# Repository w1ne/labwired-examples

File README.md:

# LabWired Examples

Real firmware, inspectable circuit diagrams, reproducible simulator oracles, and (when relevant) parametric mechanical models in [KernelCAD](https://kernelcad.com/).

This repository is for runnable hardware verification stories, **not concept art or untested AI-generated designs**. Each example states which behavior was verified, where the simulator approximates hardware, and what remains missing.

## Catalog

| Example | Firmware and electronics | Mechanics | Evidence |
| --- | --- | --- | --- |
| [ESP32-C3 OLED device — Rev A candidate](examples/displays/esp32c3-oled/) | XIAO ESP32C3 clock demo, native KiCad 10 routed carrier, full BOM and pinned firmware | Removable enclosure source and STEP/STL/3MF; full path/review checks remain unresolved | 5/5 ROM-boot assertions, matching browser-WASM frames, zero native ERC/DRC findings; no physical prototype |
| [Game Boy-compatible handheld](examples/gaming/gameboy-handheld/) | STM32F411 C firmware runs Peanut-GB and an original ROM; ILI9341 and eight controls | Shared carrier/case interfaces, attached exact-source KiCad board, 59 CAD parts and 58 fixed mates | Saved-project MCU verification, host ROM behavior, browser input, hosted native PCB DRC/attachment and static CAD checks; no physical hardware |
| [HeyPCB imported-board acceptance sample](examples/pcb/heypcb-import-acceptance/) | Seven pinned KiCad PCB files and model-gap evidence; no full-board pass | No mechanical model | Source blobs verified; seven imports reported in unmerged PR #2934; none completely simulated |
| [Industrial BLDC fault verification](examples/industrial/bldc-fault-verification/) | STM32L476 compiled C, 24 V motor plant, three digital fault flags, inverter shutdown | No mechanical model in this example | Normal spin-up and 3 fault scenarios model-verified; ideal MCU supply, no physical bench |
| [Quadrotor co-design](examples/robotics/quadrotor-bldc/) | Four STM32L476 C channels; separate native six-layer ESC with zero configured ERC/DRC findings | 36-part KernelCAD frame and four rotor joints; populated-board assembly candidate remains blocked | Candidate browser: 360 exact motor/CAD observations, isolated fault, pause and reset. Actual board simulation and flight remain open. |
| [Pathfinder hobby rocket](examples/aerospace/pathfinder-rocket/) | STM32F411 saved firmware/diagram/stimuli; 5/5 saved flight-sequence oracle clauses | Linked CAD; PCB is wider than the stated available sled width | Saved model-verified firmware; **PCB fit and physical flight blocked** |
| [AXIOM H1 humanoid controller](examples/robotics/axiom-h1/) | ESP32-C3 + two PCA9685 expanders; 20 powered servo command models and fault/E-stop evidence | 20 source-derived CAD bindings; 59 sampled poses and archived mesh replay pass | Saved powered topology; mechanical deployment pending; **physical acceptance failed** |
| [A1 mini printer](examples/fabrication/a1-mini-printer/) | STM32F411 four-axis firmware, endstops, heaters and display; 2/2 saved clauses | Linked printer CAD; native cross-domain acceptance pending | Saved firmware verified; **machine/assembly behavior unverified** |
| [P.I.G. robot arm](examples/robotics/pig-arm/) | Six PCA9685 servo channels, nine poses, limits and E-stop; 3/3 saved clauses | Physical motion/kinematics not accepted | Saved controller verified; **joint actuation not verified** |

## Featured video

[Watch the 75-second quadrotor co-design engineering preview](examples/robotics/quadrotor-bldc/media/quadrotor-engineering-preview.mp4): editable CAD, exploded assembly, native schematic/PCB, four live motor channels, a selected-channel fault, pause and reset. This is actual application footage of a candidate STM32 propulsion bench. The physical OpenESC board and aircraft flight are not simulated by that bench.

## Run

Open an example directory. The export-backed packs contain the saved LabWired firmware, circuit, stimuli, and requirements in `project.input.json`, plus revision-pinned evidence in `evidence.json`. They link to existing saved projects. Some require separate linked PCB/CAD assets or further integration. An import does **not** imply the original evidence transfers to the new project. The quadrotor and other engineering demos additionally include native sources and recorded tools.

For an introduction to firmware-aware circuit simulation, use the [LabWired circuit simulator guide](https://labwired.com/circuit-simulator/). It links to a GPIO-to-RC oscilloscope demonstration and explains the different browser linear-circuit and native ngspice capabilities. The quadrotor example above is a separate motor-control verification. For imported circuits, see the [KiCad PCB simulation guide](https://labwired.com/kicad-pcb-simulation/) and the [ESP32-S3 BME280 source-net case](https://labwired.com/kicad-pcb-simulation/#bme280-i2c-address). Import is not whole-board simulation.

## Contribution standard

New examples need catalog-validated connectivity, compilable firmware, an explicit test oracle, and precise model limits. For mechanical projects, keep editable KernelCAD source and verified joints. See [CONTRIBUTING.md](CONTRIBUTING.md).

**Core simulator and firmware-model changes belong in [w1ne/labwired-core](https://github.com/w1ne/labwired-core).** This repository stores reproducible consumers of that engine, not copies of the engine.

## Licensing

Example source and scripts are MIT licensed. Individual CAD assets may carry CC0-1.0 declarations in their metadata. Manufacturer names (including ODrive) are descriptive and do not imply endorsement, compatibility or use of proprietary software.

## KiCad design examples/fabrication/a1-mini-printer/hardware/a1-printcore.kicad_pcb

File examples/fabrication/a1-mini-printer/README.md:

# A1 mini four-axis printer

This example is exported from a **real saved LabWired project**, not a proposed design.

- [Open the original project in LabWired](https://app.labwired.com/p/4926352279d2673187b55cd5e727ff69/edit)
- [Project source, diagram, stimuli and oracle input](project.input.json)
- [Revision-pinned saved evidence](evidence.json)
- Board: `stm32f411ceu6-blackpill`
- Saved content hash: `63c92bacf144cf5ed240425d4828d8a97b2cbc9203688dc901eb56fc9221a980`
- Original simulator evidence on this exact revision: **model_verified**
- Individual saved requirement results: **2/2 verified**

## Reproduce

1. Inspect `project.input.json`, which contains the original editable firmware source, circuit/netlist, input stimuli and explicit verification requirements.
2. Use LabWired's `labwired_project_create` with the input fields, or open the original saved project above. The imported copy is **unlisted**, and it does not automatically inherit a PCB, CAD attachment or verification receipt.
3. Run `labwired_project_verify` against the copied project with the saved requirements. Inspect the returned exact content hash and all clause results. Do not treat compilation alone as verified.
4. Inspect PCB and mechanical artifacts separately in the original project; record a fresh verification when changing firmware, wiring, source, or CAD identity.

## Proven boundary

Homing, step-command counts, OLED rendering and an overtemperature fail-safe are verified in the firmware twin; live machine mechanics, PCB-to-assembly equivalence, true extrusion and physical printer operation are not.

The linked PCB/CAD items, if present, are **not** reconstructed by the project-input import. The `evidence.json` file is a readback of the original saved project on 2026-11-21, not a promise that any future deployment or new copy has passed.

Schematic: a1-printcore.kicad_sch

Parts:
C1, C2: 12p; C_0603_1608Metric
C3: 2.2u; C_0805_2012Metric
C4, C5, C6, C7, C9, C10, C30, C31, C33, C40, C41, C43, C50, C51, C53, C60, C61, C63, C106, C120: 100n; C_0603_1608Metric
C8, C107: 1u; C_0805_2012Metric
C32, C42, C52, C62: 220n; C_0603_1608Metric
C34, C44, C54, C64: 100n/50V; C_0805_2012Metric
C35, C45, C55, C65: 47u/50V; C_1210_3225Metric
C100: 470u/35V; CP_Elec_10x10.5
C101: 1u/50V; C_1210_3225Metric
C102, C103: 4.7u/50V; C_1210_3225Metric
C104, C105: 22u/10V; C_1210_3225Metric
C109, C110: 4.7u; C_0805_2012Metric
C112: 220n/50V; C_0603_1608Metric
C140, C141, C142, C143, C144: 10n; C_0603_1608Metric
D1: SMBJ33A; D_SMB
D3, D4: SS34; D_SMA
D10: PWR; LED_0603_1608Metric
D11: FAULT; LED_0603_1608Metric
F1: 25A MINI; Fuseholder_Blade_Mini_Keystone_3568
J1: 24V INPUT; AMASS_XT30PW-M_1x02_P2.50mm_Horizontal
J2: BED 24V/12A; TerminalBlock_Phoenix_MKDS-3-2-5.08_1x02_P5.08mm_Horizontal
J3: HOTEND 24V/3A; TerminalBlock_Phoenix_MKDS-3-2-5.08_1x02_P5.08mm_Horizontal
J4: FAN1; JST_XH_B2B-XH-A_1x02_P2.50mm_Vertical
J5: FAN2; JST_XH_B2B-XH-A_1x02_P2.50mm_Vertical
J10: X_MOTOR; Molex_Micro-Fit_3.0_43650-0410_1x04-1MP_P3.00mm_Horizontal
J11: Y_MOTOR; Molex_Micro-Fit_3.0_43650-0410_1x04-1MP_P3.00mm_Horizontal
J12: Z_MOTOR; Molex_Micro-Fit_3.0_43650-0410_1x04-1MP_P3.00mm_Horizontal
J13: E_MOTOR; Molex_Micro-Fit_3.0_43650-0410_1x04-1MP_P3.00mm_Horizontal
J20: USB4216-03-A; MPN USB4216-03-A
J21: SWD; PinHeader_2x05_P1.27mm_Vertical_SMD
J22: OLED I2C; JST_SH_BM04B-SRSS-TB_1x04-1MP_P1.00mm_Vertical
J23: UART; JST_SH_BM04B-SRSS-TB_1x04-1MP_P1.00mm_Vertical
J30: X END; JST_XH_B3B-XH-A_1x03_P2.50mm_Vertical
J31: Y END; JST_XH_B3B-XH-A_1x03_P2.50mm_Vertical
J32: Z END; JST_XH_B3B-XH-A_1x03_P2.50mm_Vertical
J33: BED NTC; JST_XH_B2B-XH-A_1x02_P2.50mm_Vertical
J34: HOT NTC; JST_XH_B2B-XH-A_1x02_P2.50mm_Vertical
J35: ESTOP/START; JST_XH_B4B-XH-A_1x04_P2.50mm_Vertical
L1: 10uH/3.2A; L_Bourns_SRN6045TA
Q1, Q2, Q3: AOD4184A; TO-252-3_TabPin2
Q4, Q5: AO3400A; SOT-23
R1, R33, R43, R53, R63, R105, R140, R141, R142, R152, R153: 10k; R_0603_1608Metric
R2, R100, R103, R121, R123, R125, R128, R129: 100k; R_0603_1608Metric
R3, R4: 22R; R_0603_1608Metric
R5, R6: 5.1k; R_0603_1608Metric
R7: 1M; R_0603_1608Metric
R30, R31, R40, R41, R50, R51, R60, R61: 0.10R; R_2512_6332Metric
R32, R42, R52, R62: 30.1k; R_0603_1608Metric
R34, R44, R54, R64, R104: 24.9k; R_0603_1608Metric
R120, R122, R124: 33R; R_0603_1608Metric
R126, R127: 100R; R_0603_1608Metric
R143, R144: 100k 0.1%; R_0603_1608Metric
R150, R151: 4.7k; R_0603_1608Metric
R160, R161: 1k; R_0603_1608Metric
SW1: RESET; SW_SPST_PTS810
TP1: X_VREF; TestPoint_Pad_D1.5mm
TP2: Y_VREF; TestPoint_Pad_D1.5mm
TP3: Z_VREF; TestPoint_Pad_D1.5mm
TP4: E_VREF; TestPoint_Pad_D1.5mm
TP20: 24V; TestPoint_Pad_D1.5mm
TP21: 5V; TestPoint_Pad_D1.5mm
TP22: 3V3; TestPoint_Pad_D1.5mm
TP23: GND; TestPoint_Pad_D1.5mm
U1: STM32F411CEU6; QFN-48-1EP_7x7mm_P0.5mm_EP5.6x5.6mm
U10, U11, U12, U13: A4988SETTR-T; TQFN-28-1EP_5x5mm_P0.5mm_EP3.25x3.25mm
U20: LMR36520A; SOIC-8-1EP_3.9x4.9mm_P1.27mm_EP2.41x3.3mm
U21: AP2112K-3.3; SOT-23-5
U30: 74HCT125D; SOIC-14_3.9x8.7mm_P1.27mm
U31: USBLC6-2SC6; SOT-23-6
Y1: 8MHz; Crystal_SMD_3225-4Pin_3.2x2.5mm

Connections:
+3V3: C4.1, C5.1, C6.1, C7.1, C8.1, C9.1, C10.1, C33.1, C43.1, C53.1, C63.1, C110.1, J21.1, J22.2 (VCC), J23.2, J30.2, J31.2, J32.2, J33.1 (A), J34.1 (A), J35.4, R1.1, R32.1, R42.1, R52.1, R62.1, R105.1, R140.1, R141.1, R142.1, R150.1, R151.1, R152.1, R153.1, R160.1, R161.1, TP22.1, U1.1 (VBAT), U1.9 (VDDA), U1.24 (VDD), U1.36 (VDD), U1.48 (VDD), U10.12 (RESET), U10.14 (SLEEP), U10.15 (VDD), U11.12 (RESET), U11.14 (SLEEP), U11.15 (VDD), U12.12 (RESET), U12.14 (SLEEP), U12.15 (VDD), U13.12 (RESET), U13.14 (SLEEP), U13.15 (VDD), U21.5 (VOUT)
+5V: C104.1, C105.1, C109.1, C120.1, L1.2, R103.1, TP21.1, U21.1 (VIN), U21.3 (EN), U30.14 (VCC)
+24V: C31.2, C34.1, C35.1, C41.2, C44.1, C45.1, C51.2, C54.1, C55.1, C61.2, C64.1, C65.1, C100.1, C101.1, C102.1, C103.1, C112.1, D1.1 (K), D3.1 (K), D4.1 (K), F1.2, J2.1, J3.1, J4.1 (+), J5.1, R100.1, TP20.1, U10.22 (VMOT), U10.28 (VMOT), U11.22 (VMOT), U11.28 (VMOT), U12.22 (VMOT), U12.28 (VMOT), U13.22 (VMOT), U13.28 (VMOT), U20.2 (VIN)
+24VIN: F1.1, J1.1 (+)
BED_CMD: U1.27 (PB14), U30.5
BED_GATE: R120.1, R122.1, U30.6
BED_GATE_A: Q1.1 (G), R120.2, R121.1
BED_GATE_B: Q2.1 (G), R122.2, R123.1
BED_SW: J2.2, Q1.2 (D), Q2.2 (D)
BOOT0: R2.1, U1.44 (BOOT0)
BUCK_BOOT: C106.1, U20.7 (BOOT)
BUCK_EN: R100.2, U20.3 (EN)
BUCK_FB: R103.2, R104.1, U20.5 (FB)
BUCK_PG: R105.2, U20.4 (PG)
BUCK_SW: C106.2, L1.1, U20.8 (SW)
BUCK_VCC: C107.1, U20.6 (VCC)
CC1: J20.A5 (3), R5.1
CC2: J20.B5 (4), R6.1
DRV_EN: U1.25 (PB12), U10.2 (EN), U11.2 (EN), U12.2 (EN), U13.2 (EN)
END_X: C140.1, J30.3, R140.2, U1.29 (PA8)
END_Y: C141.1, J31.3, R141.2, U1.2 (PC13)
END_Z: C142.1, J32.3, R142.2, U1.3 (PC14)
ESTOP: J35.2, R152.2, U1.20 (PB2)
E_A+: J13.1 (1A), U13.24 (1A)
E_A-: J13.2 (1B), U13.21 (1B)
E_B+: J13.3 (2A), U13.26 (2A)
E_B-: J13.4 (2B), U13.1 (2B)
E_CP1: C60.1, U13.4 (CP1)
E_CP2: C60.2, U13.5 (CP2)
E_DIR: U1.21 (PB10), U13.19 (DIR)
E_ROSC: R64.1, U13.13 (ROSC)
E_S1: R60.1, U13.23 (SENSE1)
E_S2: R61.1, U13.27 (SENSE2)
E_STEP: U1.46 (PB9), U13.16 (STEP)
E_VCP: C61.1, U13.6 (VCP)
E_VREF: R62.2, R63.1, TP4.1, U13.17 (REF)
E_VREG: C62.1, U13.8 (VREG)
FAN1_CMD: U1.28 (PB15), U30.9
FAN1_GATE: R126.1, U30.8
FAN1_GATE_Q: Q4.1 (G), R126.2, R128.1
FAN1_SW: D3.2 (A), J4.2 (-), Q4.3 (D)
FAN2_CMD: U1.10 (PA0), U30.12
FAN2_GATE: R127.1, U30.11
FAN2_GATE_Q: Q5.1 (G), R127.2, R129.1
FAN2_SW: D4.2 (A), J5.2, Q5.3 (D)
GND: C1.2, C2.2, C3.2, C4.2, C5.2, C6.2, C7.2, C8.2, C9.2, C10.2, C32.2, C33.2, C34.2, C35.2, C42.2, C43.2, C44.2, C45.2, C52.2, C53.2, C54.2, C55.2, C62.2, C63.2, C64.2, C65.2, C100.2, C101.2, C102.2, C103.2, C104.2, C105.2, C107.2, C109.2, C110.2, C112.2, C120.2, C140.2, C141.2, C142.2, C143.2, C144.2, D1.2 (A), D10.1 (K), J1.2 (-), J20.A1 (1), J20.A12 (1), J20.B1 (1), J20.B12 (1), J20.SH (1), J21.3, J21.5 (3), J21.9 (3), J22.1 (GND), J23.1, J30.1, J31.1, J32.1, J35.1, Q1.3 (S), Q2.3 (S), Q3.3 (S), Q4.2 (S), Q5.2 (S), R2.2, R5.2, R6.2, R7.2, R30.2, R31.2, R33.2, R34.2, R40.2, R41.2, R43.2, R44.2, R50.2, R51.2, R53.2, R54.2, R60.2, R61.2, R63.2, R64.2, R104.2, R121.2, R123.2, R125.2, R128.2, R129.2, R143.2, R144.2, SW1.2, TP23.1, U1.8 (VSSA), U1.23 (VSS), U1.35 (VSS), U1.47 (VSS), U1.49 (VSS), U10.3 (GND), U10.9 (MS1), U10.10 (MS2), U10.11 (MS3), U10.18 (GND), U10.29 (GND), U11.3 (GND), U11.9 (MS1), U11.10 (MS2), U11.11 (MS3), U11.18 (GND), U11.29 (GND), U12.3 (GND), U12.9 (MS1), U12.10 (MS2), U12.11 (MS3), U12.18 (GND), U12.29 (GND), U13.3 (GND), U13.9 (MS1), U13.10 (MS2), U13.11 (MS3), U13.18 (GND), U13.29 (GND), U20.1 (PGND), U20.9 (PAD), U21.2 (GND), U30.1, U30.4, U30.7 (GND), U30.10, U30.13, U31.2 (GND), Y1.2, Y1.4
HOTEND_CMD: U1.26 (PB13), U30.2
HOT_GATE: R124.1, U30.3
HOT_GATE_Q: Q3.1 (G), R124.2, R125.1
HOT_SW: J3.2, Q3.2 (D)
I2C_SCL: J22.3 (SCL), R150.2, U1.42 (PB6)
I2C_SDA: J22.4 (SDA), R151.2, U1.43 (PB7)
LED_FAULT_A: D11.2 (A), R161.2
LED_PWR_A: D10.2 (A), R160.2
NC_LDO: U21.4 (NC)
NC_PC15: U1.4 (PC15)
NC_SBU1: J20.A8 (7)
NC_SBU2: J20.B8 (8)
NC_SWD7: J21.7 (6)
NC_SWD8: J21.8 (7)
NRST: J21.10 (8), R1.2, SW1.1, U1.7 (NRST)
OSC_IN: C1.1, U1.5 (PH0), Y1.1
OSC_OUT: C2.1, U1.6 (PH1), Y1.3
SPI_MISO: U1.16 (PA6)
SPI_MOSI: U1.17 (PA7)
SPI_SCK: U1.15 (PA5)
START: J35.3, R153.2, U1.38 (PA15)
SWCLK: J21.4, U1.37 (PA14)
SWDIO: J21.2, U1.34 (PA13)
TH_BED: C143.1, J33.2 (B), R143.1, U1.11 (PA1)
TH_HOT: C144.1, J34.2 (B), R144.1, U1.14 (PA4)
UART_RX: J23.4, U1.13 (PA3)
UART_TX: J23.3, U1.12 (PA2)
USB_DM: R3.2, U1.32 (PA11)
USB_DM_CONN: J20.A7 (6), J20.B7 (6), U31.1 (IO1_A)
USB_DM_MCU: R3.1, U31.6 (IO1_B)
USB_DP: R4.2, U1.33 (PA12)
USB_DP_CONN: J20.A6 (5), J20.B6 (5), U31.3 (IO2_A)
USB_DP_MCU: R4.1, U31.4 (IO2_B)
USB_VBUS: J20.A4 (2), J20.A9 (2), J20.B4 (2), J20.B9 (2), U31.5 (VBUS)
USB_VBUS_SENSE: R7.1, U1.30 (PA9)
USER_AUX: D11.1 (K), U1.31 (PA10)
VCAP1: C3.1, U1.22 (VCAP_1)
X_A+: J10.1 (1A), U10.24 (1A)
X_A-: J10.2 (1B), U10.21 (1B)
X_B+: J10.3 (2A), U10.26 (2A)
X_B-: J10.4 (2B), U10.1 (2B)
X_CP1: C30.1, U10.4 (CP1)
X_CP2: C30.2, U10.5 (CP2)
X_DIR: U1.19 (PB1), U10.19 (DIR)
X_ROSC: R34.1, U10.13 (ROSC)
X_S1: R30.1, U10.23 (SENSE1)
X_S2: R31.1, U10.27 (SENSE2)
X_STEP: U1.18 (PB0), U10.16 (STEP)
X_VCP: C31.1, U10.6 (VCP)
X_VREF: R32.2, R33.1, TP1.1, U10.17 (REF)
X_VREG: C32.1, U10.8 (VREG)
Y_A+: J11.1 (1A), U11.24 (1A)
Y_A-: J11.2 (1B), U11.21 (1B)
Y_B+: J11.3 (2A), U11.26 (2A)
Y_B-: J11.4 (2B), U11.1 (2B)
Y_CP1: C40.1, U11.4 (CP1)
Y_CP2: C40.2, U11.5 (CP2)
Y_DIR: U1.40 (PB4), U11.19 (DIR)
Y_ROSC: R44.1, U11.13 (ROSC)
Y_S1: R40.1, U11.23 (SENSE1)
Y_S2: R41.1, U11.27 (SENSE2)
Y_STEP: J21.6 (5), U1.39 (PB3), U11.16 (STEP)
Y_VCP: C41.1, U11.6 (VCP)
Y_VREF: R42.2, R43.1, TP2.1, U11.17 (REF)
Y_VREG: C42.1, U11.8 (VREG)
Z_A+: J12.1 (1A), U12.24 (1A)
Z_A-: J12.2 (1B), U12.21 (1B)
Z_B+: J12.3 (2A), U12.26 (2A)
Z_B-: J12.4 (2B), U12.1 (2B)
Z_CP1: C50.1, U12.4 (CP1)
Z_CP2: C50.2, U12.5 (CP2)
Z_DIR: U1.45 (PB8), U12.19 (DIR)
Z_ROSC: R54.1, U12.13 (ROSC)
Z_S1: R50.1, U12.23 (SENSE1)
Z_S2: R51.1, U12.27 (SENSE2)
Z_STEP: U1.41 (PB5), U12.16 (STEP)
Z_VCP: C51.1, U12.6 (VCP)
Z_VREF: R52.2, R53.1, TP3.1, U12.17 (REF)
Z_VREG: C52.1, U12.8 (VREG)

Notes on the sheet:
MCU / USB
POWER INPUT / REGULATORS
X AXIS
Y AXIS
Z AXIS
EXTRUDER
HEATERS / FANS
I/O / CONTROLS
J10 MP x2: mechanical retention, no net
J11 MP x2: mechanical retention, no net
J12 MP x2: mechanical retention, no net
J13 MP x2: mechanical retention, no net
J22 MP x2: mechanical retention, no net
J23 MP x2: mechanical retention, no net
External supply intent: J1 24 V through F1; USB host VBUS; common return. Flags are nonphysical.

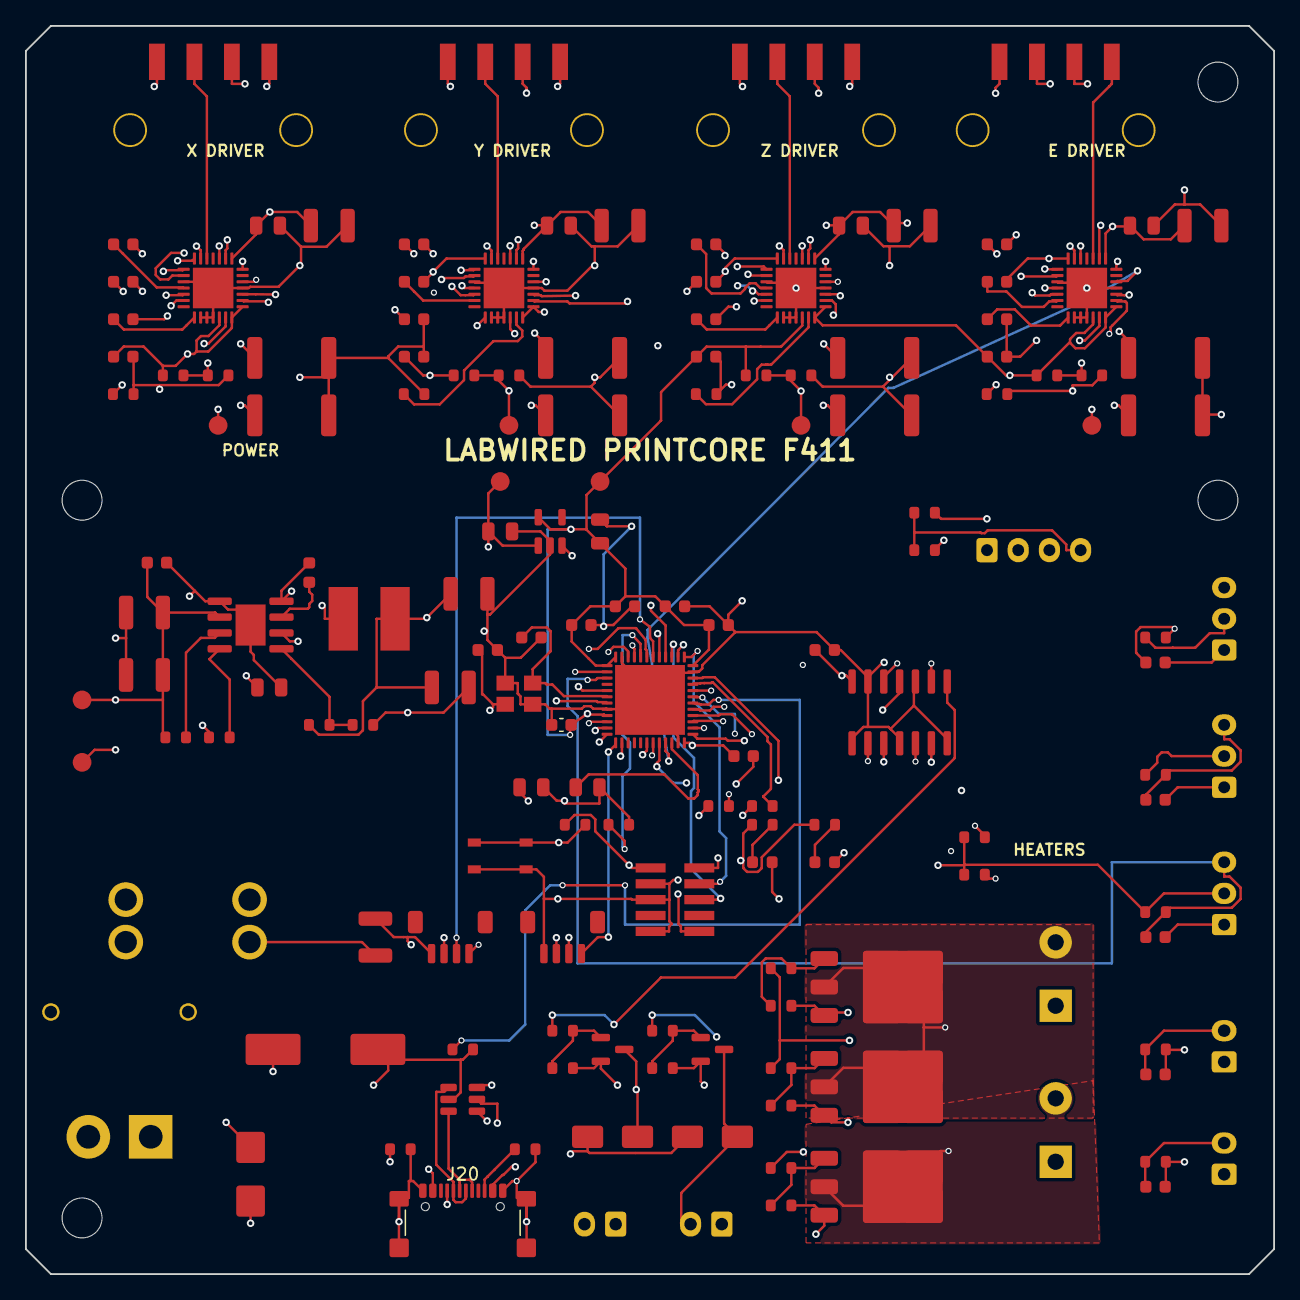
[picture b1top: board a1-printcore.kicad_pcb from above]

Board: 4 copper layers, 100.0 x 100.0 mm, 157 parts (0 on the bottom side), 116 nets.

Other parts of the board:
H1, H2, H3, H4: M3; MountingHole_3.2mm_M3

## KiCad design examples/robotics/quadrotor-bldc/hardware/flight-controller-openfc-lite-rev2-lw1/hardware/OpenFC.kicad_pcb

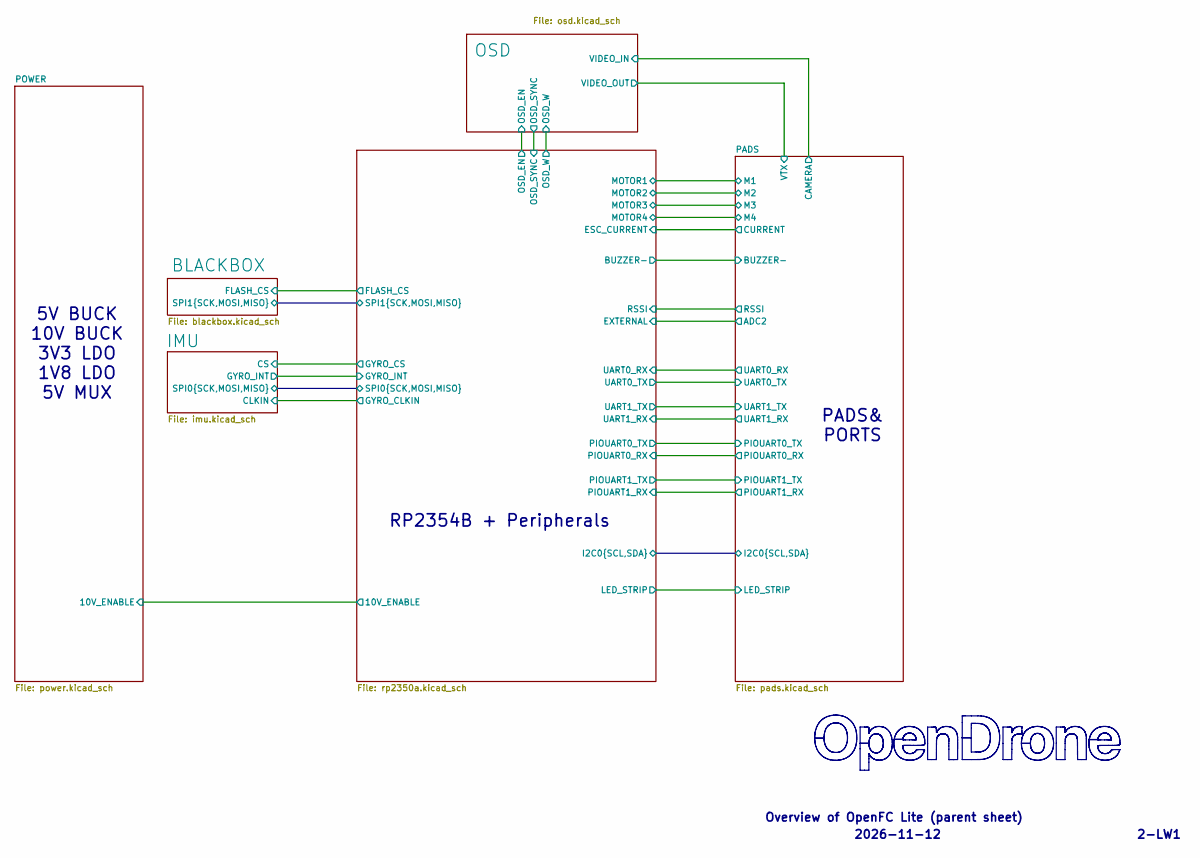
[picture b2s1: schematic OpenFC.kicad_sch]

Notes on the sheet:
Overview of OpenFC Lite (parent sheet)
5V BUCK 10V BUCK 3V3 LDO 1V8 LDO 5V MUX
2-LW1
2026-11-12
RP2354B + Peripherals
PADS& PORTS

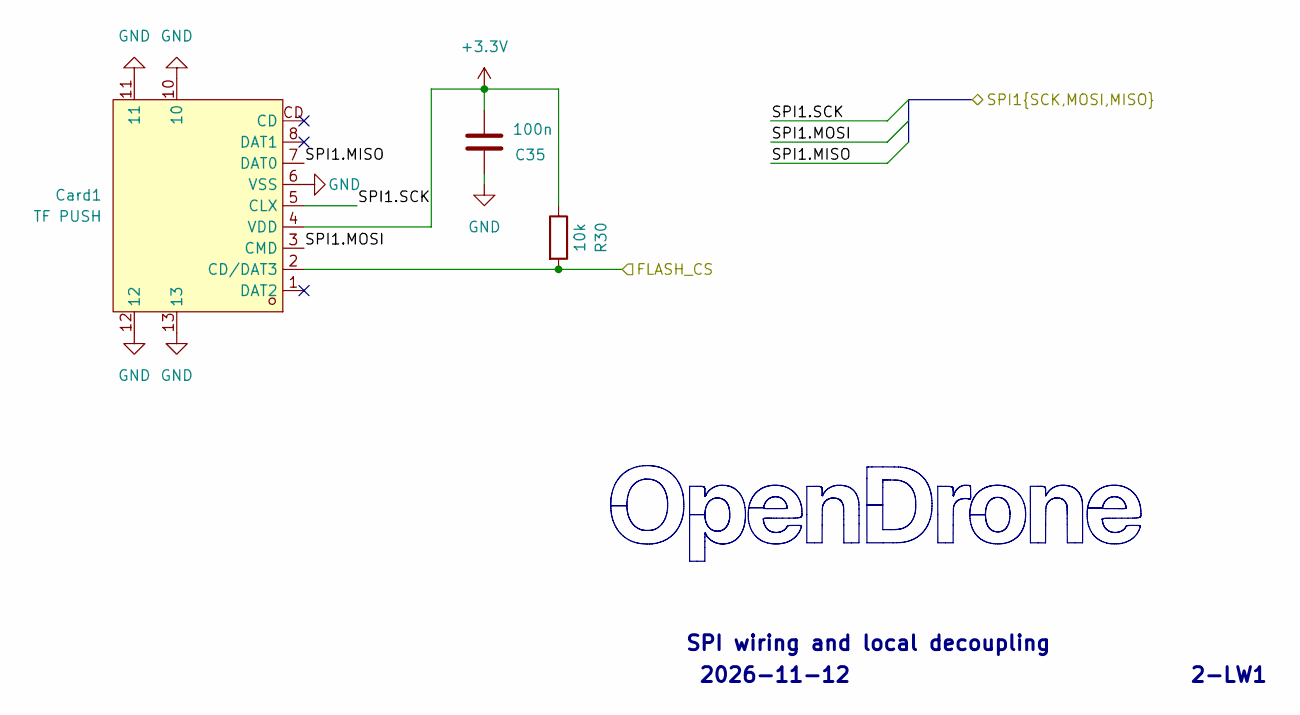
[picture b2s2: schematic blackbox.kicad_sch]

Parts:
C35: 100n; C_0201_0603Metric; MPN GRM033R61E104KE14D; LCSC C76939
Card1: TF PUSH; TF-SMD_TF-PUSH; MPN TF PUSH; LCSC C393941
R30: 10k; R_0201_0603Metric; MPN RC0201FR-0710KL; LCSC C106225

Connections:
+3.3V: C35.1, Card1.4 (VDD), R30.1; also elsewhere on the board
/BLACKBOX/FLASH_CS: Card1.2 (CD/DAT3), R30.2; also elsewhere on the board
/BLACKBOX/SPI1.MISO: Card1.7 (DAT0); also elsewhere on the board
/BLACKBOX/SPI1.MOSI: Card1.3 (CMD); also elsewhere on the board
/BLACKBOX/SPI1.SCK: Card1.5 (CLX); also elsewhere on the board
GND: C35.2, Card1.6 (VSS), Card1.10, Card1.11, Card1.12, Card1.13; also elsewhere on the board

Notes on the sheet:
SPI wiring and local decoupling
2026-11-12
2-LW1

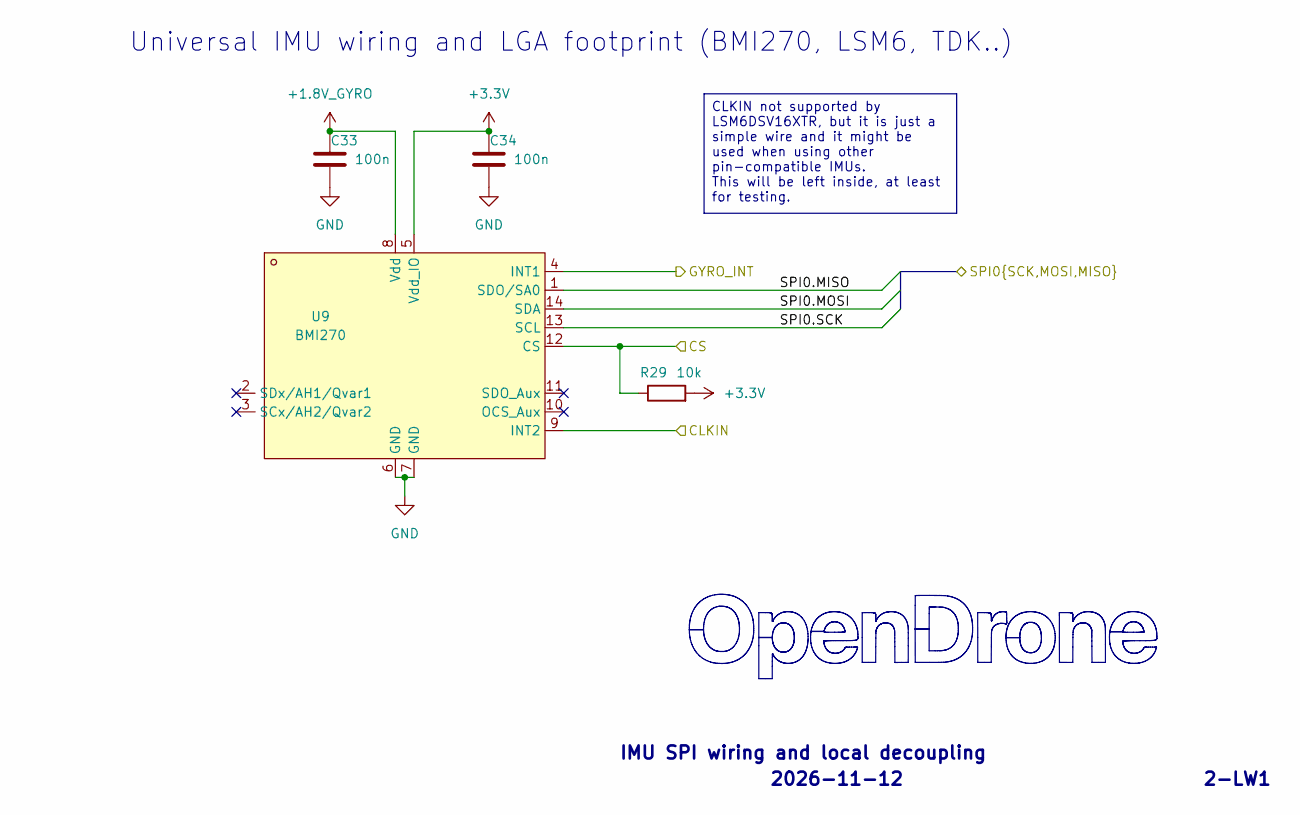
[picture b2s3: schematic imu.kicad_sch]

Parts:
C33, C34: 100n; C_0201_0603Metric; MPN GRM033R61E104KE14D; LCSC C76939
R29: 10k; R_0201_0603Metric; MPN RC0201FR-0710KL; LCSC C106225
U9: BMI270; LGA-14_L3.0-W2.5-P0.50-BR; MPN BMI270; LCSC C2836813

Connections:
+1.8V_GYRO: C33.1, U9.8 (VDD); also elsewhere on the board
+3.3V: C34.1, R29.2, U9.5 (VDDIO); also elsewhere on the board
/IMU/CLKIN: U9.9 (INT2); also elsewhere on the board
/IMU/CS: R29.1, U9.12 (CSB); also elsewhere on the board
/IMU/GYRO_INT: U9.4 (INT1); also elsewhere on the board
/IMU/SPI0.MISO: U9.1 (SDO); also elsewhere on the board
/IMU/SPI0.MOSI: U9.14 (SDx); also elsewhere on the board
/IMU/SPI0.SCK: U9.13 (SCx); also elsewhere on the board
GND: C33.2, C34.2, U9.6 (GNDIO), U9.7 (GND); also elsewhere on the board

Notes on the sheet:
2-LW1
2026-11-12
IMU SPI wiring and local decoupling
Universal IMU wiring and LGA footprint (BMI270, LSM6, TDK..)
CLKIN not supported by LSM6DSV16XTR, but it is just a simple wire and it might be used when using other pin-compatible IMUs. This will be left inside, at least for testing.

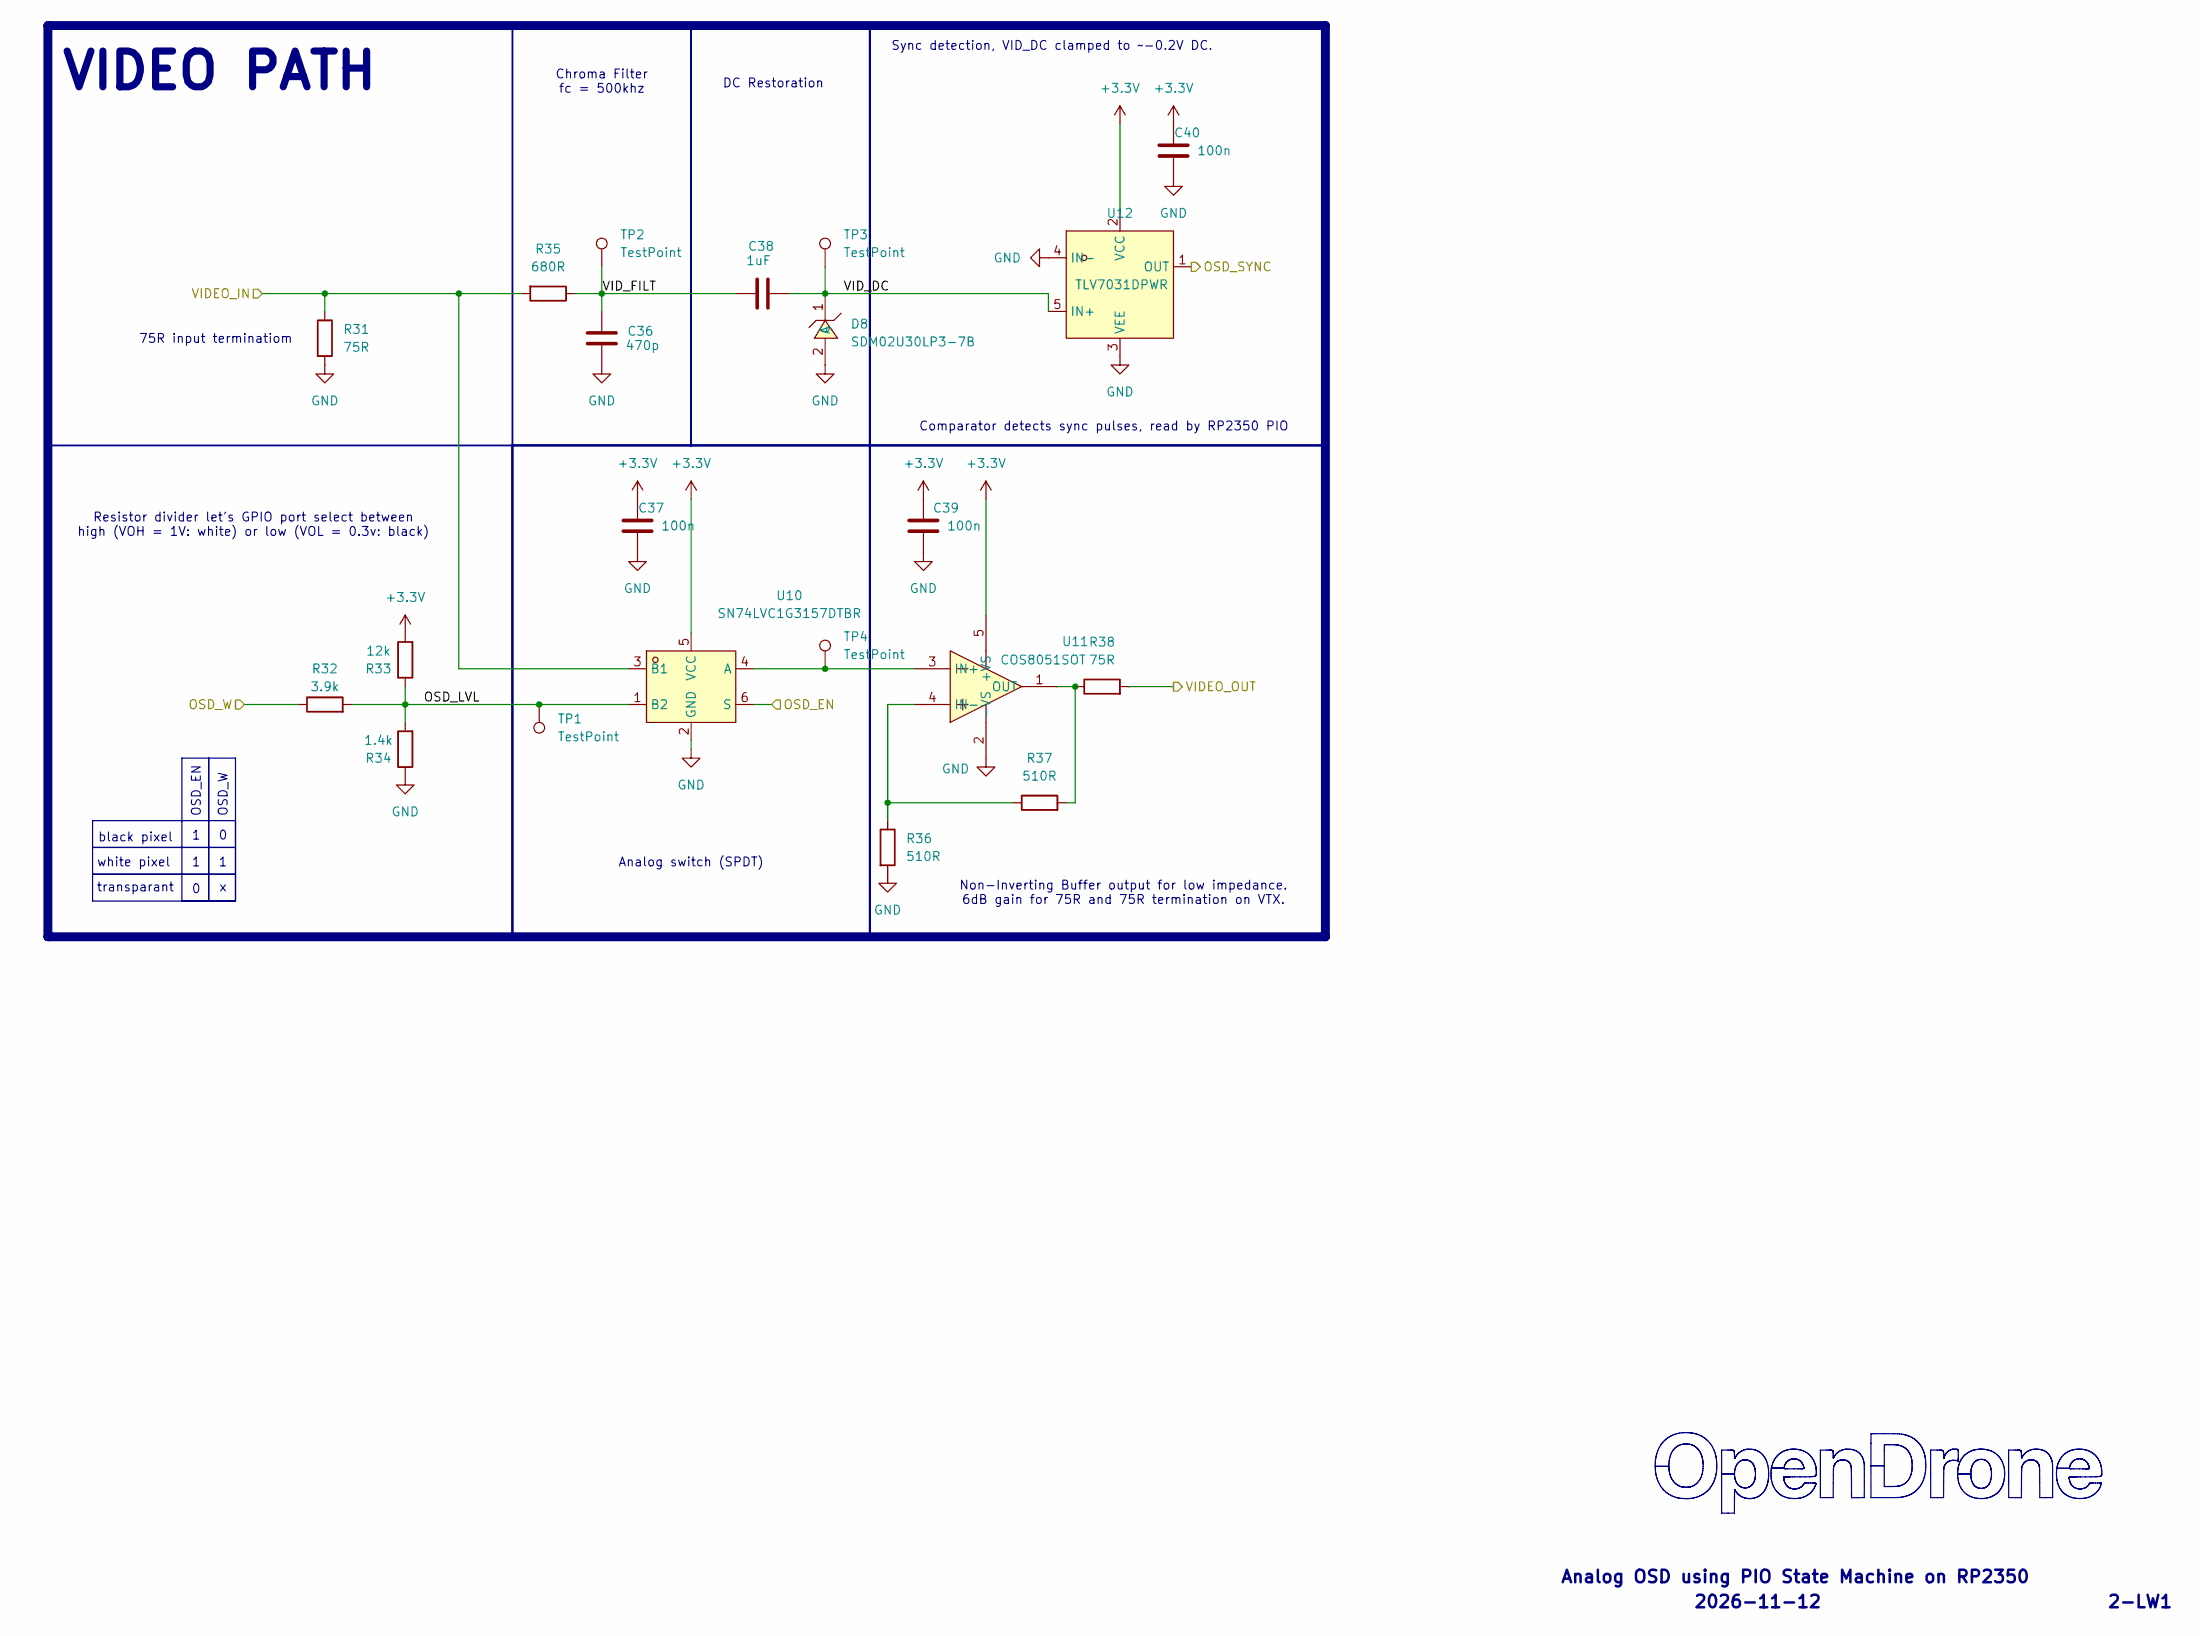
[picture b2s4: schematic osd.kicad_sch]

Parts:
C36: 470p; C_0201_0603Metric; MPN CC0201JRX7R9BB471; LCSC C526944
C37, C39, C40: 100n; C_0201_0603Metric; MPN GRM033R60J104KE19D; LCSC C76928
C38: 1uF; C_0402_1005Metric; MPN CL05A105KA5NQNC; LCSC C52923
D8: SDM02U30LP3-7B; X3-DFN0603-2_L0.6-W0.3-RD; MPN SDM02U30LP3-7B; LCSC C151629
R31, R38: 75R; R_0201_0603Metric; MPN RC0201FR-0775RL; LCSC C274878
R32: 3.9k; R_0201_0603Metric; MPN RC0201FR-073K9L; LCSC C273280
R33: 12k; R_0201_0603Metric; MPN 0201WMF1202TEE; LCSC C270363
R34: 1.4k; R_0201_0603Metric; MPN 0201WMF1401TEE; LCSC C423739
R35: 680R; R_0201_0603Metric; MPN 0201WMF6800TEE; LCSC C473509
R36, R37: 510R; R_0201_0603Metric; MPN RC0201FR-07510RL; LCSC C57784
TP1, TP2, TP3, TP4: TestPoint; TestPoint_Pad_D1.5mm
U10: SN74LVC1G3157DTBR; TI_DTB0006A_RevC_SMD; MPN SN74LVC1G3157DTBR; LCSC C2673087
U11: COS8051SOT; SOT-23-5_L3.0-W1.7-P0.95-LS2.8-BR; MPN COS8051SOT; LCSC C7463385
U12: TLV7031DPWR; TI_DPW0005A_X2SON-5_0.8x0.8mm; MPN TLV7031DPWR; LCSC C2876045

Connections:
+3.3V: C37.1, C39.1, C40.1, R33.2, U10.5 (VCC), U11.5 (+VS), U12.2 (VCC); also elsewhere on the board
/OSD/OSD_EN: U10.6 (S); also elsewhere on the board
/OSD/OSD_LVL: R32.2, R33.1, R34.2, TP1.1, U10.1 (B2)
/OSD/OSD_SYNC: U12.1 (OUT); also elsewhere on the board
/OSD/OSD_W: R32.1; also elsewhere on the board
/OSD/VIDEO_IN: R31.1, R35.2, U10.3 (B1); also elsewhere on the board
/OSD/VIDEO_OUT: R38.2; also elsewhere on the board
/OSD/VID_DC: C38.2, D8.1 (C), TP3.1, U12.5 (IN+)
/OSD/VID_FILT: C36.1, C38.1, R35.1, TP2.1
GND: C36.2, C37.2, C39.2, C40.2, D8.2 (A), R31.2, R34.1, R36.2, U10.2 (GND), U11.2 (-VS), U12.3 (VEE), U12.4 (IN-); also elsewhere on the board
unnamed: TP4.1, U10.4 (A), U11.3 (IN+)
unnamed: R36.1, R37.1, U11.4 (IN-)
unnamed: R37.2, R38.1, U11.1 (OUT)

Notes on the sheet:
black pixel
Comparator detects sync pulses, read by RP2350 PIO
2026-11-12
Analog OSD using PIO State Machine on RP2350
Sync detection, VID_DC clamped to ~-0.2V DC.
Non-Inverting Buffer output for low impedance. 6dB gain for 75R and 75R termination on VTX.
2-LW1
white pixel
75R input terminatiom
OSD_W
Chroma Filter fc = 500khz
VIDEO PATH
Analog switch (SPDT)
OSD_EN
transparant
DC Restoration
Resistor divider let's GPIO port select between high (VOH = 1V: white) or low (VOL = 0.3v: black)

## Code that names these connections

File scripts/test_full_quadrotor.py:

"""Source identity, wiring and command-failsafe checks for the five-MCU twin.

These tests do not claim that five-firmware physics execution was validated.
"""
from __future__ import annotations

import hashlib
import json
from pathlib import Path
import shutil
import subprocess
import tempfile
import unittest

ROOT = Path(__file__).resolve().parents[1]
QUAD = ROOT / "examples/robotics/quadrotor-bldc"


class FullQuadrotorCandidate(unittest.TestCase):
    @classmethod
    def setUpClass(cls):
        cls.diagram = json.loads((QUAD / "labwired/five-controller-flight-circuit.json").read_text())
        cls.manifest = json.loads((QUAD / "labwired/five-controller-flight-project.json").read_text())
        cls.fc_source = (QUAD / "firmware/flight/fc.c").read_text()

    def test_exactly_five_source_bound_firmware_instances(self):
        channels = self.manifest["channels"]
        self.assertEqual({c["controller"] for c in channels}, {"fc", "ctrl1", "ctrl2", "ctrl3", "ctrl4"})
        self.assertEqual(len(channels), 5)
        for c in channels:
            source = (QUAD / c["source"]).read_bytes()
            self.assertEqual(hashlib.sha256(source).hexdigest(), c["source_sha256"])
            self.assertEqual(len(source), c["source_bytes"])
            self.assertEqual(c["board"], "stm32l476")

    def test_four_motors_full_wiring_and_imu(self):
        parts = {p["id"]: p for p in self.diagram["parts"]}
        self.assertEqual(len(parts), 17)
        self.assertEqual(len(self.diagram["wires"]), 81)
        self.assertEqual(parts["fc"]["type"], "nucleo-l476rg")
        self.assertEqual(parts["imu"]["type"], "bmi270")
        self.assertEqual(parts["kill"]["type"], "button-module")
        self.assertEqual(parts["fc"]["attrs"]["internal_pullups"], "PB6,PB7")
        # The connected MCP diagram schema requires string-valued attrs.
        for part in parts.values():
            self.assertTrue(all(isinstance(value, str) for value in part.get("attrs", {}).values()))
        edges = {(w["from"]["part"], w["from"]["pin"], w["to"]["part"], w["to"]["pin"])
                 for w in self.diagram["wires"]}
        for index in range(1, 5):
            ctrl, rotor, fault = f"ctrl{index}", f"rotor{index}", f"fault{index}"
            self.assertEqual(parts[ctrl]["type"], "nucleo-l476rg")
            self.assertEqual(parts[rotor]["type"], "bldc-motor")
            self.assertEqual(parts[fault]["type"], "button-module")
            self.assertIn(("fc", f"PC{index+7}", ctrl, "PA0"), edges)
            self.assertIn((ctrl, "PB0", "fc", f"PC{index-1}"), edges)
            self.assertIn((ctrl, "PB7", fault, "SIG"), edges)
            for mcu_pin, motor_pin in (("PA8", "AH"), ("PB13", "AL"),
                                       ("PA9", "BH"), ("PB14", "BL"),
                                       ("PA10", "CH"), ("PB15", "CL"),
                                       ("PB0", "ENABLE"), ("PC0", "HALL_A"),
                                       ("PC1", "HALL_B"), ("PC2", "HALL_C")):
                self.assertIn((ctrl, mcu_pin, rotor, motor_pin), edges)
        for a, b in (("PB6", "SCL"), ("PB7", "SDA")):
            self.assertIn(("fc", a, "imu", b), edges)
        self.assertIn(("fc", "PC4", "kill", "SIG"), edges)

    def test_commanded_esc_pwm_and_hall_cadence_is_not_mislabelled(self):
        escs = [(QUAD / f"firmware/flight/esc{i}.c").read_text() for i in range(1, 5)]
        for i, esc in enumerate(escs, start=1):
            self.assertTrue(esc.startswith(f"#define ESC_ID {i}\n"))
            self.assertIn("#define CPU_HZ 4000000u", esc)
            self.assertIn("#define PWM_HZ 1000u", esc)
            self.assertIn("#define PWM_PERIOD_TICKS (CPU_HZ/((3u+1u)*PWM_HZ))", esc)
            self.assertIn("TIM1_PSC=3;TIM1_ARR=PWM_PERIOD_TICKS-1u", esc)
            self.assertIn("TIM1_BDTR=0x30;", esc)
            self.assertIn("if(++motor_phase<20u)continue; motor_phase=0;", esc)
            self.assertIn("if(startup_t%5==0)", esc)
            self.assertIn("period>=1&&period<=20", esc)
            self.assertNotIn("TIM1_BDTR=MOE|0x30;", esc)
            self.assertIn("start_inverter()", esc)
            self.assertIn("stop_inverter()", esc)
        profile = self.manifest["esc_behavioral_profile"]
        self.assertEqual(profile["cpu_hz"] // ((profile["timer_prescaler"] + 1) *
            (profile["timer_auto_reload"] + 1)), profile["inverter_pwm_hz"])
        self.assertEqual(profile["inverter_pwm_hz"], 1000)
        self.assertEqual(profile["hall_control_hz"], 500)

    def test_failsafe_paths_are_latched_before_logging(self):
        self.assertIn('"FC OPERATOR KILL - ALL ESC DISARM', self.fc_source)
        self.assertIn('"FC IMU LOST - ALL ESC DISARM', self.fc_source)
        self.assertIn('"FC ESC NOT READY - ALL ESC DISARM', self.fc_source)
        self.assertIn('"FC FAULT DETECTED - ALL ESC DISARM', self.fc_source)
        latch = self.fc_source.split('static void latch_disarm(', 1)[1].split('static uint8_t clamp_width', 1)[0]
        self.assertLess(latch.index('GPIOC_ODR &= ~COMMAND_MASK;'), latch.index('text(reason);'))
        self.assertIn('command_high_mask(phase, widths)', self.fc_source)
        # A scheduled text marker is not proof of movement, and a previously
        # grounded craft must never report an actual landing after an abort.
        self.assertIn('if (ticks == 2u * TICKS_PER_SECOND && !failsafe) text("FC TAKEOFF COMMAND', self.fc_source)
        self.assertIn('if (failsafe && takeoff_verified && !landing_verified', self.fc_source)
        self.assertNotIn('text("FC TAKEOFF\\r\\n")', self.fc_source)
        self.assertIn('FC ESTIMATED GROUND CONTACT', self.fc_source)
        self.assertNotIn('SAFE LANDING VERIFIED', self.fc_source)

    @unittest.skipUnless(shutil.which("cc"), "host C compiler unavailable")
    def test_pwm_zero_command_clears_all_four_pins(self):
        # Includes the actual target implementation. Rename its main so the
        # pure command bitmask can be tested without MCU register access.
        harness = r'''
#define main flight_controller_entry
#include "fc.c"
#undef main
#include <assert.h>
int main(void) {
    const uint8_t widths[4] = {18, 40, 72, 0};
    const uint8_t disabled[4] = {0, 0, 0, 0};
    assert(command_high_mask(0, widths) == ((1u<<8)|(1u<<9)|(1u<<10)));
    assert(command_high_mask(17, widths) == ((1u<<8)|(1u<<9)|(1u<<10)));
    assert(command_high_mask(18, widths) == ((1u<<9)|(1u<<10)));
    assert(command_high_mask(40, widths) == (1u<<10));
    assert(command_high_mask(72, widths) == 0);
    assert(command_high_mask(40, disabled) == 0);
    assert(command_high_mask(0, disabled) == 0);
    return 0;
}
'''
        with tempfile.TemporaryDirectory() as folder:
            directory = Path(folder)
            source = directory / "pwm_test.c"
            binary = directory / "pwm_test"
            source.write_text(harness)
            subprocess.run(["cc", "-std=c11", "-Wall", "-Wextra", "-Werror", "-O2",
                            "-I", str(QUAD / "firmware/flight"), str(source), "-o", str(binary)],
                           check=True, capture_output=True, text=True)
            subprocess.run([str(binary)], check=True, capture_output=True, text=True)


if __name__ == "__main__":
    unittest.main()

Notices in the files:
examples/gaming/esp32s3-doom/README.md:
Sources and licenses:
- [Espressif PCB v1.0 guide](https://documentation.espressif.com/esp-dev-kits/en/latest/esp32s3/esp32-s3-devkitc-1/user_guide_v1.0.html), [native DXF](https://dl.espressif.com/dl/DXF_ESP32-S3-DevKitC-1_V1_20210312CB.dxf) and [factory schematic](https://dl.espressif.com/dl/SCH_ESP32-S3-DEVKITC-1_V1_20210312C.pdf).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
examples/industrial/iolink-station/README.md:
Licensing:
New package source and authored board files use the repository MIT license.
ST dependencies retain their included vendor licenses. The linked firmware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
